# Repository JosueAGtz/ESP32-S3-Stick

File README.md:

# ESP32-S3 Stick

ESP32-S3 is a dual-core XTensa LX7 MCU, capable of running at 240 MHz. Apart from its 512 KB of internal SRAM, it also comes with integrated 2.4 GHz, 802.11 b/g/n Wi-Fi and Bluetooth 5 (LE) connectivity that provides long-range support. It has 45 programmable GPIOs and supports a rich set of peripherals.

## ESP32-S3 Stick Pinout

## ESP32-S3 Stick Features

## ESP32-S3 Stick Dimmensions

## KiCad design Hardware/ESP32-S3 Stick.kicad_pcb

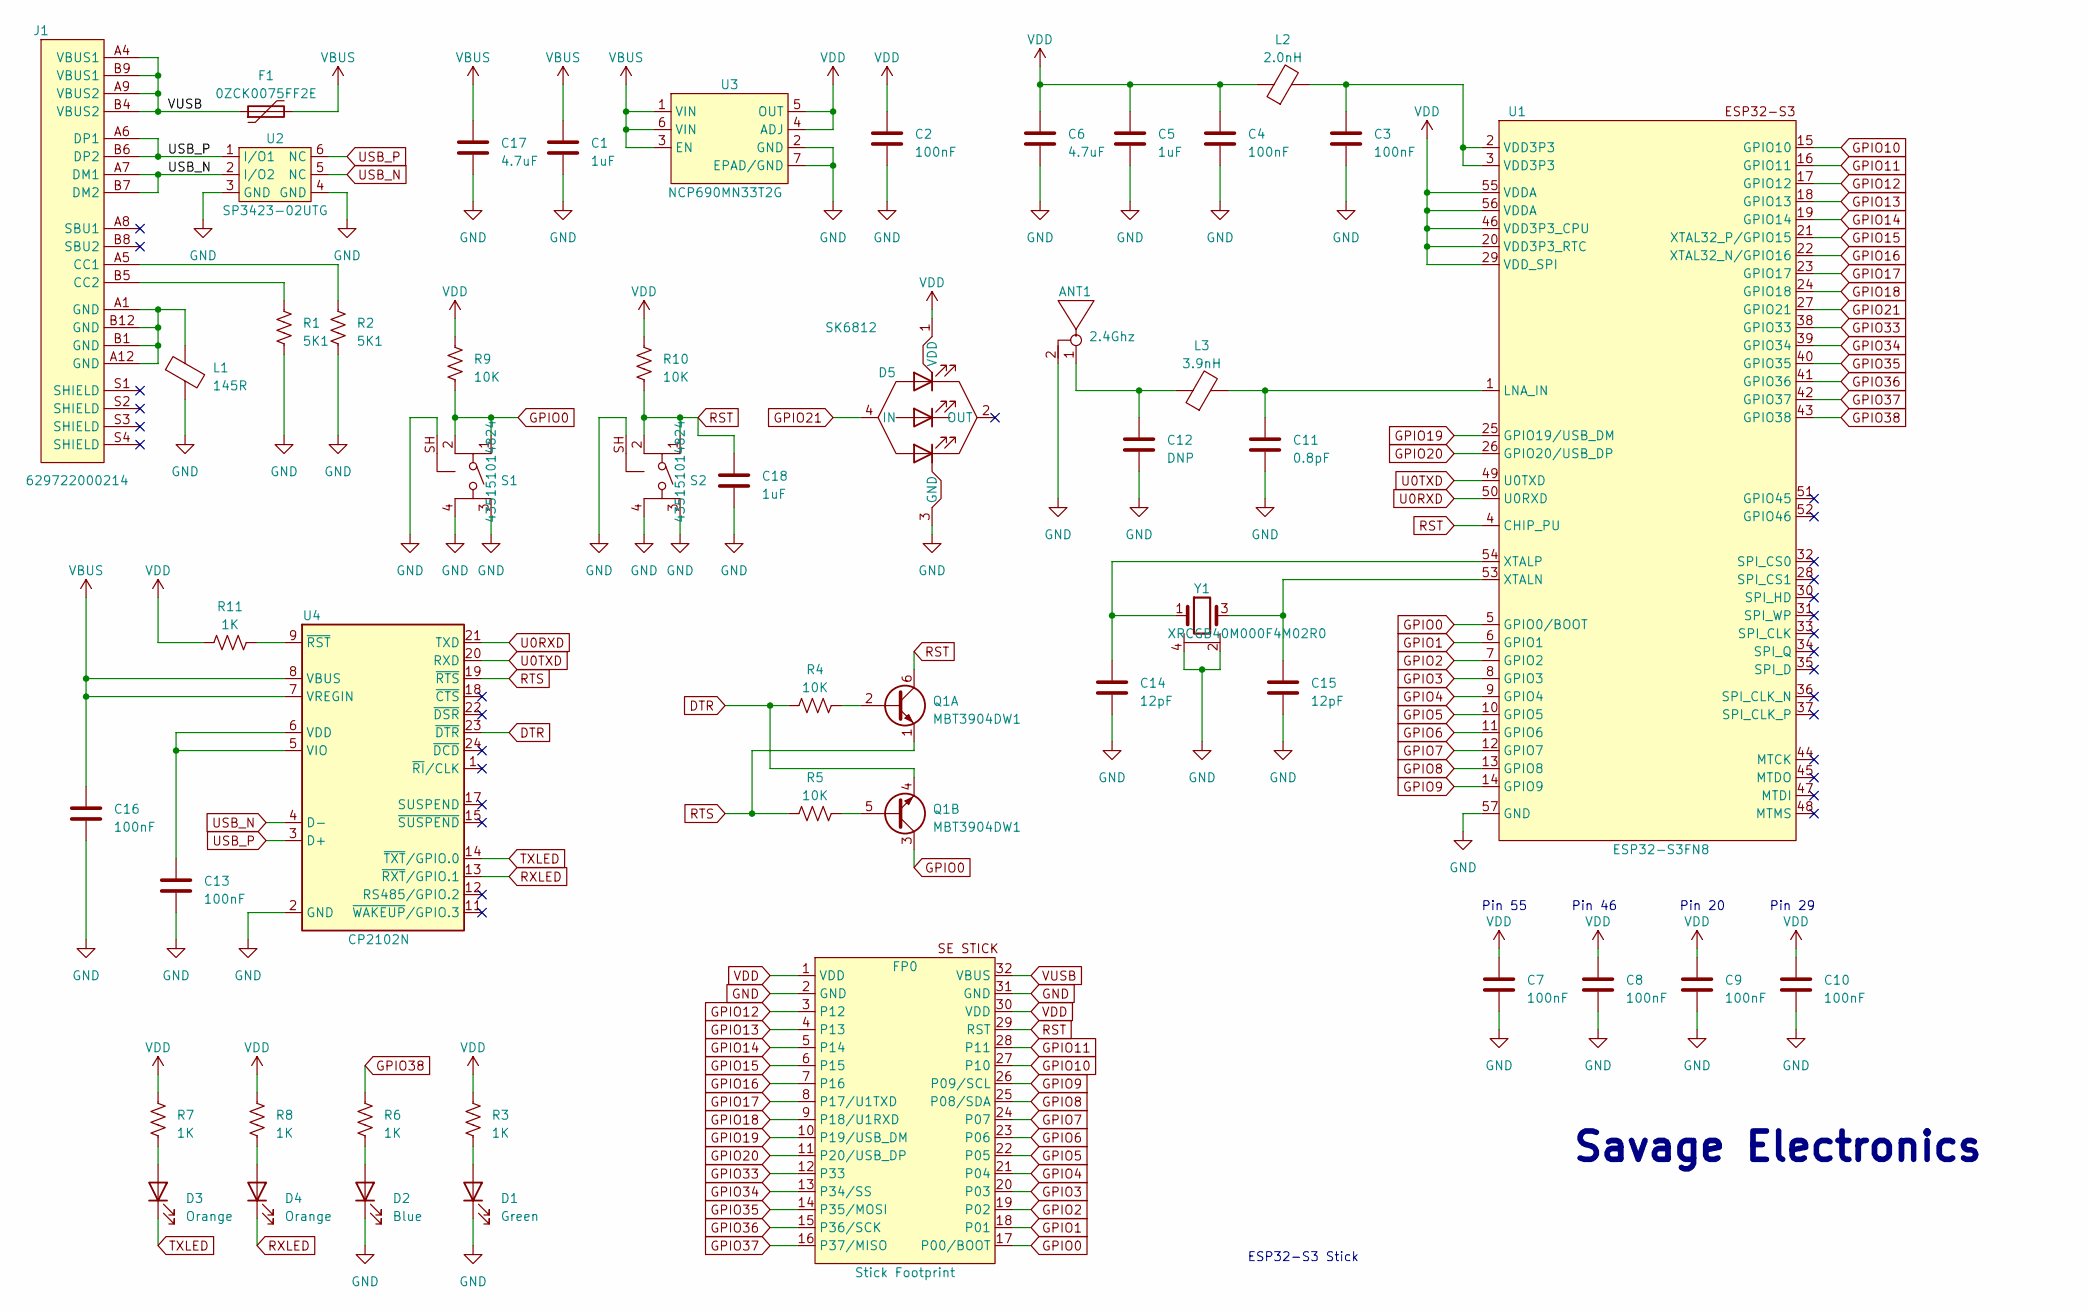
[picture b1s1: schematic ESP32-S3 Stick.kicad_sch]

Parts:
ANT1: 2.4Ghz; PCB_Ant24
C1, C5, C18: 1uF; C_0402_1005Metric
C2, C3, C4, C7, C8, C9, C10, C13, C16: 100nF; C_0402_1005Metric
C6, C17: 4.7uF; C_0402_1005Metric
C11: 0.8pF; C_0402_1005Metric
C12: DNP; C_0402_1005Metric
C14, C15: 12pF; C_0402_1005Metric
D1: Green; 0402LED
D2: Blue; 0402LED
D3, D4: Orange; 0402LED
D5: SK6812; SK6812_2X2mm
F1: 0ZCK0075FF2E; Fuse_0805_2012Metric
FP0: Stick Footprint; Stick
J1: 629722000214; USBC 2.0
L1: 145R; L_0402_1005Metric
L2: 2.0nH; L_0402_1005Metric
L3: 3.9nH; L_0402_1005Metric
Q1: MBT3904DW1; SC70_6P
R1, R2: 5K1; R_0402_1005Metric
R3, R6, R7, R8, R11: 1K; R_0402_1005Metric
R4, R5, R9, R10: 10K; R_0402_1005Metric
S1, S2: 435151014824
U1: ESP32-S3FN8; QFN-56-1EP_7x7mm_P0.4mm_EP4x4mm_ThermalVias_ ESP32-S3
U2: SP3423-02UTG
U3: NCP690MN33T2G; DFN6_P1MM_EP
U4: CP2102N; QFN24_4X4MM_P05_EP26
Y1: XRCGB40M000F4M02R0; SMD_4PADS_20X16

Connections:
DTR: Q1.4 (E2), R4.1, U4.23 (~DTR)
GND: ANT1.2, C1.2, C2.2, C3.2, C4.2, C5.2, C6.2, C7.2, C8.2, C9.2, C10.2, C11.2, C12.2, C13.2, C14.2, C15.2, C16.2, C17.2, C18.2, D1.1 (K), D2.1 (K), D5.3 (GND), FP0.2 (GND), FP0.31 (GND), L1.2, R1.2, R2.2, S1.3, S1.4, S1.SH, S2.3, S2.4, S2.SH, U1.57 (GND), U2.3 (GND), U2.4 (GND), U3.2 (GND), U3.7 (EPAD/GND), U4.2 (GND), U4.25 (GND), Y1.2, Y1.4
GPIO0: FP0.17 (P00/BOOT), Q1.3 (C2), R9.2, S1.1, S1.2, U1.5 (GPIO0/BOOT)
GPIO1: FP0.18 (P01), U1.6 (GPIO1)
GPIO2: FP0.19 (P02), U1.7 (GPIO2)
GPIO3: FP0.20 (P03), U1.8 (GPIO3)
GPIO4: FP0.21 (P04), U1.9 (GPIO4)
GPIO5: FP0.22 (P05), U1.10 (GPIO5)
GPIO6: FP0.23 (P06), U1.11 (GPIO6)
GPIO7: FP0.24 (P07), U1.12 (GPIO7)
GPIO8: FP0.25 (P08/SDA), U1.13 (GPIO8)
GPIO9: FP0.26 (P09/SCL), U1.14 (GPIO9)
GPIO10: FP0.27 (P10), U1.15 (GPIO10)
GPIO11: FP0.28 (P11), U1.16 (GPIO11)
GPIO12: FP0.3 (P12), U1.17 (GPIO12)
GPIO13: FP0.4 (P13), U1.18 (GPIO13)
GPIO14: FP0.5 (P14), U1.19 (GPIO14)
GPIO15: FP0.6 (P15), U1.21 (XTAL32_P/GPIO15)
GPIO16: FP0.7 (P16), U1.22 (XTAL32_N/GPIO16)
GPIO17: FP0.8 (P17/U1TXD), U1.23 (GPIO17)
GPIO18: FP0.9 (P18/U1RXD), U1.24 (GPIO18)
GPIO19: FP0.10 (P19/USB_DM), U1.25 (GPIO19/USB_DM)
GPIO20: FP0.11 (P20/USB_DP), U1.26 (GPIO20/USB_DP)
GPIO21: D5.4 (IN), U1.27 (GPIO21)
GPIO33: FP0.12 (P33), U1.38 (GPIO33)
GPIO34: FP0.13 (P34/SS), U1.39 (GPIO34)
GPIO35: FP0.14 (P35/MOSI), U1.40 (GPIO35)
GPIO36: FP0.15 (P36/SCK), U1.41 (GPIO36)
GPIO37: FP0.16 (P37/MISO), U1.42 (GPIO37)
GPIO38: R6.1, U1.43 (GPIO38)
unnamed: ANT1.1, C12.1, L3.1
unnamed: C3.1, L2.2, U1.2 (VDD3P3), U1.3 (VDD3P3)
unnamed: D1.2 (A), R3.2
unnamed: D2.2 (A), R6.2
unnamed: D3.2 (A), R7.2
unnamed: D4.2 (A), R8.2
unnamed: J1.A5 (CC1), R2.1
unnamed: J1.B5 (CC2), R1.1
unnamed: J1.A1 (GND), J1.A12 (GND), J1.B1 (GND), J1.B12 (GND), L1.1
unnamed: Q1.2 (B1), R4.2
unnamed: Q1.5 (B2), R5.2
unnamed: C11.1, L3.2, U1.1 (LNA_IN)
unnamed: C15.1, U1.53 (XTALN), Y1.3
unnamed: C14.1, U1.54 (XTALP), Y1.1
unnamed: C13.1, U4.5 (VIO), U4.6 (VDD)
unnamed: R11.2, U4.9 (~RST)
RST: C18.1, FP0.29 (RST), Q1.6 (C1), R10.2, S2.1, S2.2, U1.4 (CHIP_PU)
RTS: Q1.1 (E1), R5.1, U4.19 (~RTS)
RXLED: D4.1 (K), U4.13 (~RXT/GPIO.1)
TXLED: D3.1 (K), U4.14 (~TXT/GPIO.0)
U0RXD: U1.50 (U0RXD), U4.21 (TXD)
U0TXD: U1.49 (U0TXD), U4.20 (RXD)
USB_N: J1.A7 (DM1), J1.B7 (DM2), U2.2 (I/O2), U2.5 (NC), U4.4 (D-)
USB_P: J1.A6 (DP1), J1.B6 (DP2), U2.1 (I/O1), U2.6 (NC), U4.3 (D+)
VBUS: C1.1, C16.1, C17.1, F1.2, U3.1 (VIN), U3.3 (EN), U3.6 (VIN), U4.7 (VREGIN), U4.8 (VBUS)
VDD: C2.1, C4.1, C5.1, C6.1, C7.1, C8.1, C9.1, C10.1, D5.1 (VDD), FP0.1 (VDD), FP0.30 (VDD), L2.1, R3.1, R7.1, R8.1, R9.1, R10.1, R11.1, U1.20 (VDD3P3_RTC), U1.29 (VDD_SPI), U1.46 (VDD3P3_CPU), U1.55 (VDDA), U1.56 (VDDA), U3.4 (ADJ), U3.5 (OUT)
VUSB: F1.1, FP0.32 (VBUS), J1.A4 (VBUS1), J1.A9 (VBUS2), J1.B4 (VBUS2), J1.B9 (VBUS1)

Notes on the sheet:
Pin 55
Pin 29
ESP32-S3 Stick
Pin 20
Savage Electronics
Pin 46

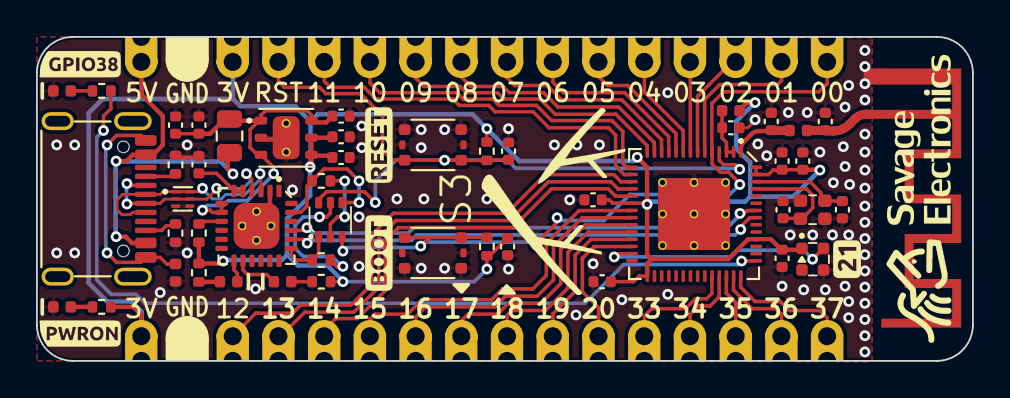
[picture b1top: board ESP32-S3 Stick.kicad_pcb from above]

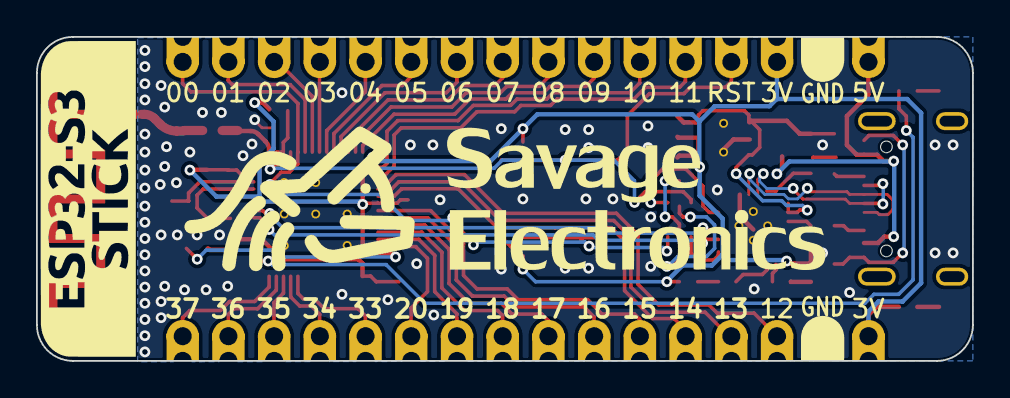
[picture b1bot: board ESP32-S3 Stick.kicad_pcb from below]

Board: 2 copper layers, 52.0 x 18.0 mm, 58 parts (2 on the bottom side), 57 nets.

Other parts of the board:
G_antennaLogo: LOGO; G_S3_ANT_LOGO
G_boot: LOGO; G_BOOT
G_gpio38: LOGO; G_GPIO38
G_logoSmall: LOGO; G_SELOGO_SMALL
G_neopixel: LOGO; G_NEOPIXEL
G_pwron: LOGO; G_PWRON
G_reset: LOGO; G_RESET
G_sticks: LOGO; G_STICKS
e: LOGO; G_SELOGO_MED
